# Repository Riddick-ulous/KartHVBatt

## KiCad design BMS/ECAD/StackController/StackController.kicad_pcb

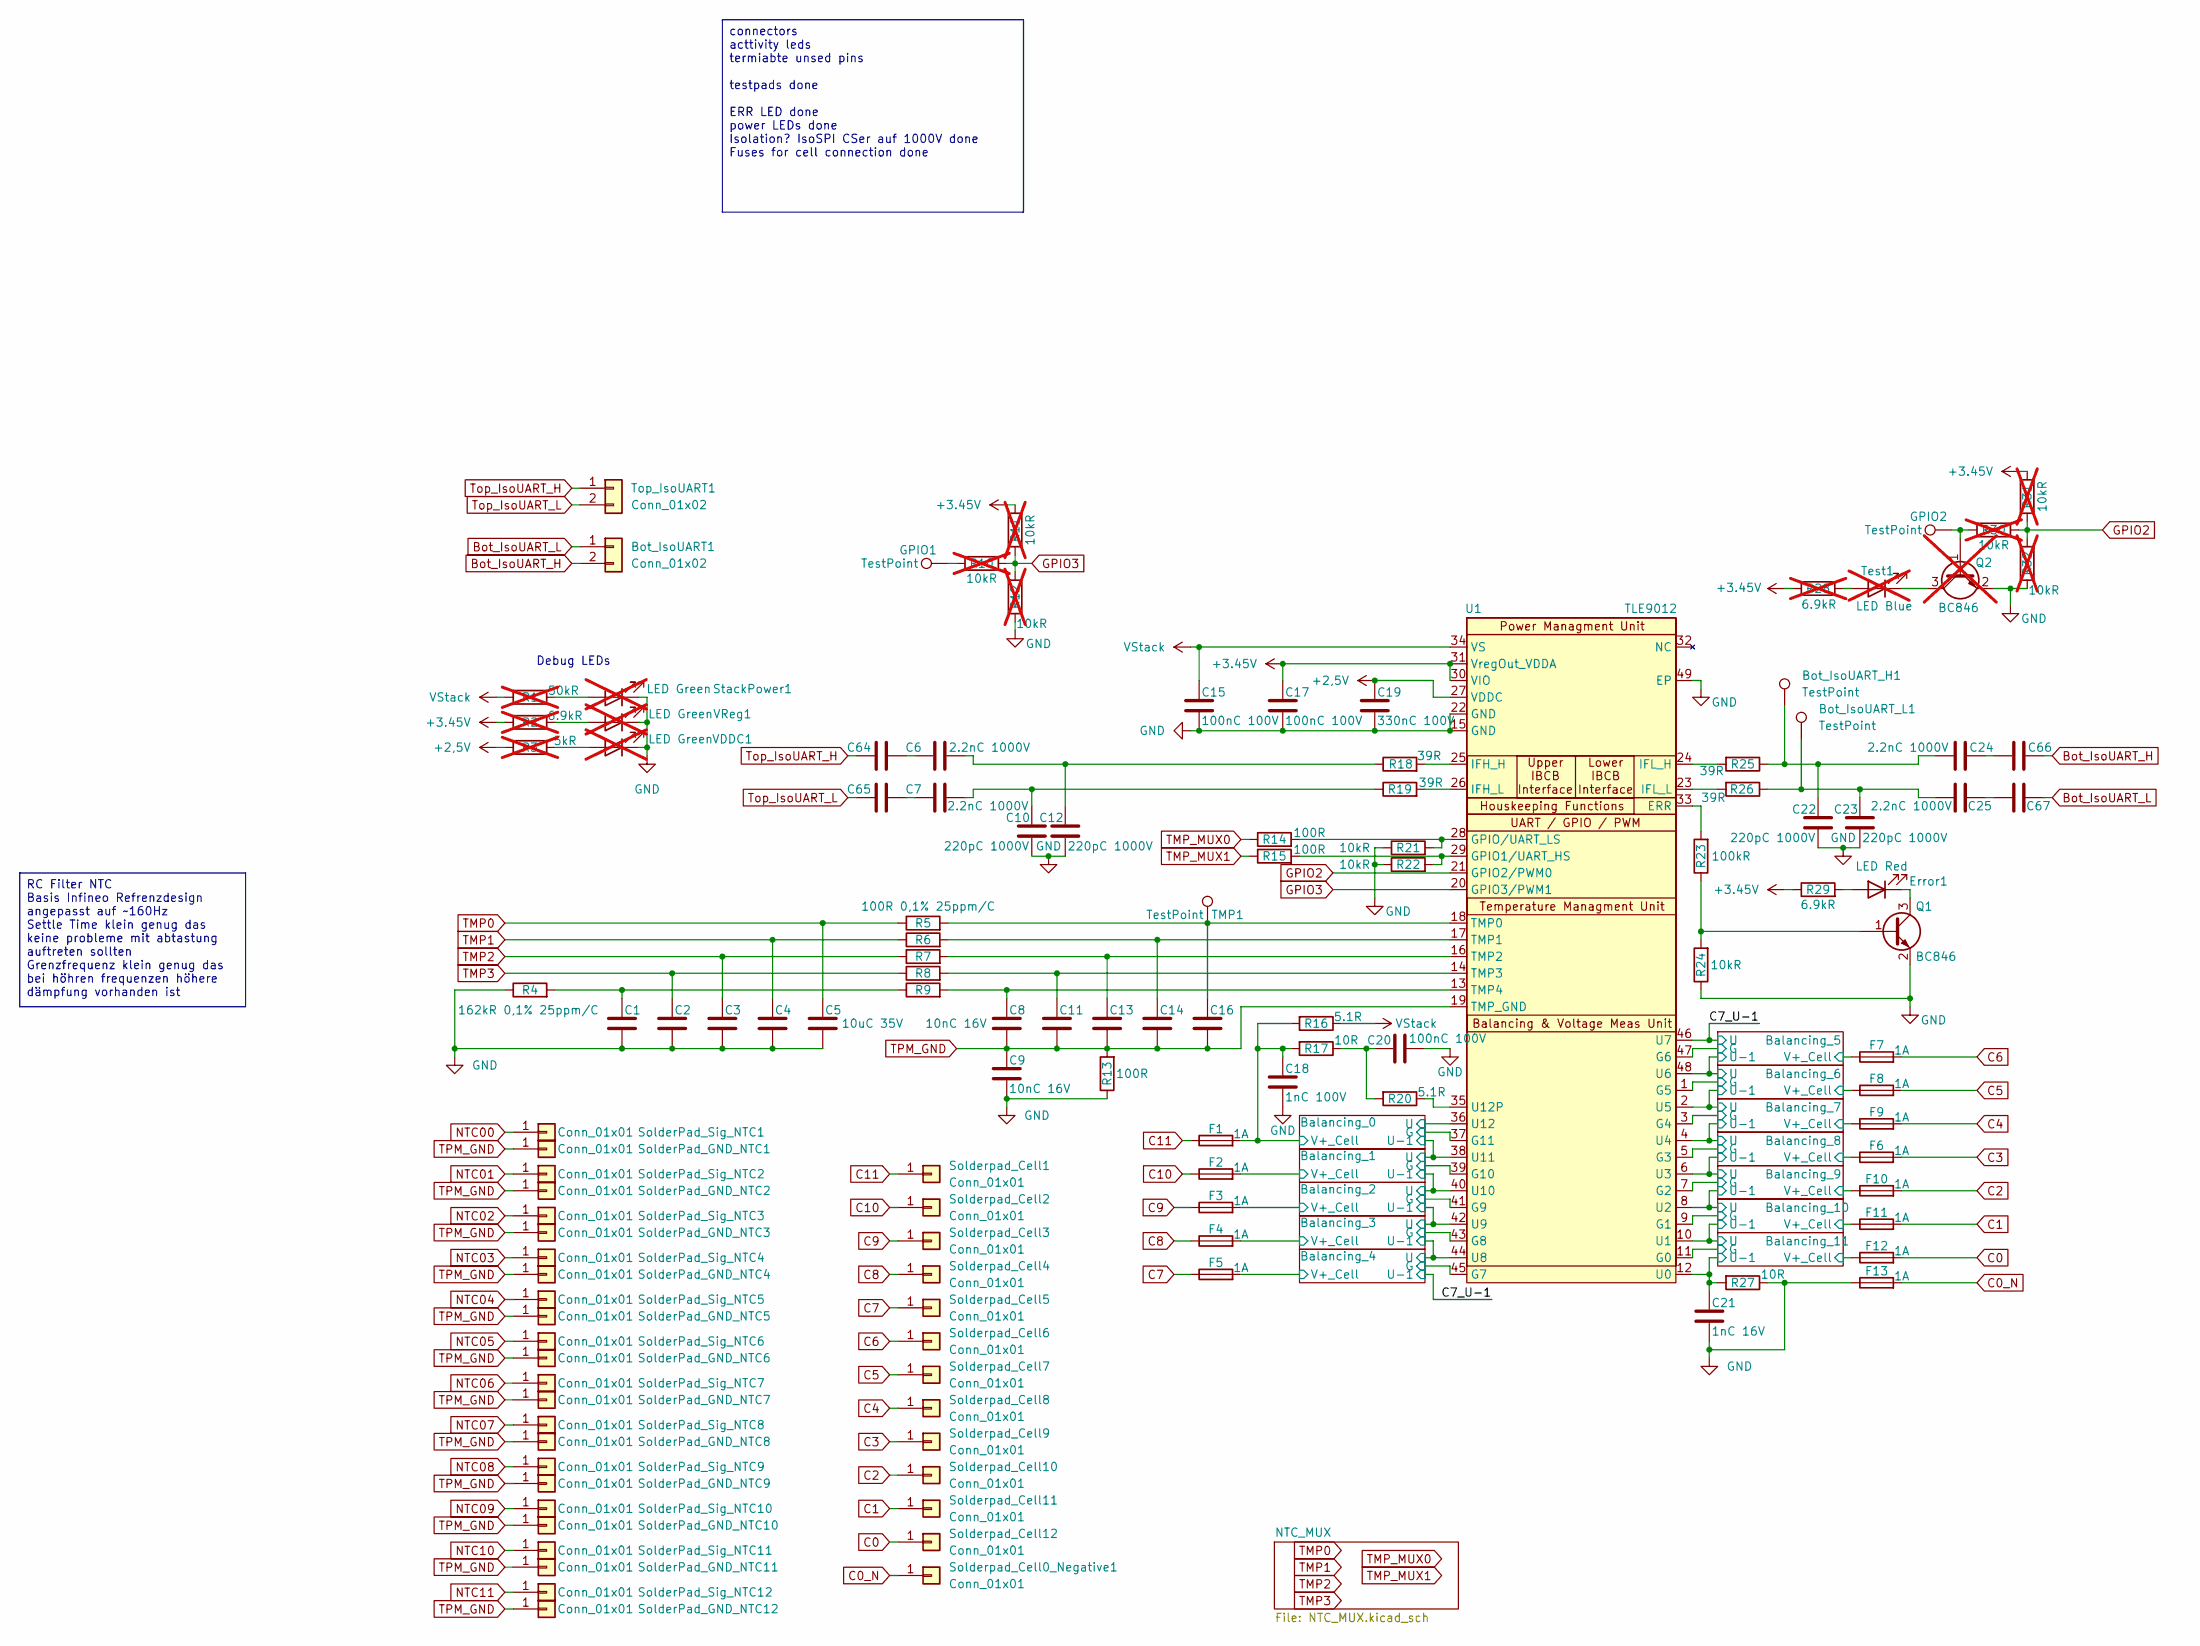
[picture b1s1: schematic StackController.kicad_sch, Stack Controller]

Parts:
Bot_IsoUART1: Conn_01x02; Molex_Micro-Fit_3.0_43045-0200_2x01_P3.00mm_Horizontal
Bot_IsoUART_H1: TestPoint; TestPoint_Loop_D1.80mm_Drill1.0mm_Beaded
Bot_IsoUART_L1: TestPoint; TestPoint_Loop_D1.80mm_Drill1.0mm_Beaded
C1, C2, C3, C4, C5: 10uC 35V; C_0805_2012Metric
C6, C7, C24, C25, C64, C65, C66, C67: 2.2nC 1000V; C_1206_3216Metric
C8, C9, C11, C13, C14, C16: 10nC 16V; C_0603_1608Metric
C10, C12, C22, C23: 220pC 1000V; C_1206_3216Metric
C15, C17, C20: 100nC 100V; C_0603_1608Metric
C18: 1nC 100V; C_0603_1608Metric
C19: 330nC 100V; C_0603_1608Metric
C21: 1nC 16V; C_0603_1608Metric
Error1: LED Red; LED_0805_2012Metric_Pad1.15x1.40mm_HandSolder
F1, F2, F3, F4, F5, F6, F7, F8, F9, F10, F11, F12, F13: 1A; Fuse_0603_1608Metric
GPIO1, GPIO2: TestPoint; TestPoint_Loop_D1.80mm_Drill1.0mm_Beaded
Q1: BC846; SOT-23
Q2: BC846; SOT-23; not fitted
R1: 50kR; R_0603_1608Metric; not fitted
R2, R28: 6.9kR; R_0603_1608Metric; not fitted
R3: 5kR; R_0603_1608Metric; not fitted
R4: 162kR 0,1% 25ppm/C; R_0603_1608Metric
R5, R6, R7, R8, R9: 100R 0,1% 25ppm/C; R_0603_1608Metric
R10, R11, R12, R30, R31, R32: 10kR; R_0603_1608Metric; not fitted
R13, R14, R15: 100R; R_0603_1608Metric
R16, R20: 5.1R; R_2512_6332Metric
R17, R27: 10R; R_2512_6332Metric
R18, R19, R25, R26: 39R; R_0603_1608Metric
R21, R22, R24: 10kR; R_0603_1608Metric
R23: 100kR; R_0603_1608Metric
R29: 6.9kR; R_0603_1608Metric
SolderPad_GND_NTC1, SolderPad_GND_NTC2, SolderPad_GND_NTC3, SolderPad_GND_NTC4, SolderPad_GND_NTC5, SolderPad_GND_NTC6, SolderPad_GND_NTC7, SolderPad_GND_NTC8, SolderPad_GND_NTC9, SolderPad_GND_NTC10, SolderPad_GND_NTC11, SolderPad_GND_NTC12: Conn_01x01; TestPoint_Pad_D1.5mm
SolderPad_Sig_NTC1, SolderPad_Sig_NTC2, SolderPad_Sig_NTC3, SolderPad_Sig_NTC4, SolderPad_Sig_NTC5, SolderPad_Sig_NTC6, SolderPad_Sig_NTC7, SolderPad_Sig_NTC8, SolderPad_Sig_NTC9, SolderPad_Sig_NTC10, SolderPad_Sig_NTC11, SolderPad_Sig_NTC12: Conn_01x01; TestPoint_Pad_D1.5mm
Solderpad_Cell0_Negative1, Solderpad_Cell1, Solderpad_Cell2, Solderpad_Cell3, Solderpad_Cell4, Solderpad_Cell5, Solderpad_Cell6, Solderpad_Cell7, Solderpad_Cell8, Solderpad_Cell9, Solderpad_Cell10, Solderpad_Cell11, Solderpad_Cell12: Conn_01x01; TestPoint_Pad_D3.0mm
StackPower1: LED Green; LED_0805_2012Metric_Pad1.15x1.40mm_HandSolder; not fitted
TMP1: TestPoint; TestPoint_Loop_D1.80mm_Drill1.0mm_Beaded
Test1: LED Blue; LED_0805_2012Metric_Pad1.15x1.40mm_HandSolder; not fitted
Top_IsoUART1: Conn_01x02; Molex_Micro-Fit_3.0_43045-0200_2x01_P3.00mm_Horizontal
U1: TLE9012; TQFP-48-1EP_7x7mm_P0.5mm_EP5x5mm
VDDC1: LED Green; LED_0805_2012Metric_Pad1.15x1.40mm_HandSolder; not fitted
VReg1: LED Green; LED_0805_2012Metric_Pad1.15x1.40mm_HandSolder; not fitted

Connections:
+2,5V: C19.1, R3.1, U1.27 (VDDC)
+3.45V: C17.1, R2.1, R11.2, R28.2, R29.1, R31.2, U1.30 (VIO), U1.31 (VregOut_VDDA)
/Balancing_0/G: U1.37 (G11); also elsewhere on the board
/Balancing_0/U: U1.36 (U12); also elsewhere on the board
/Balancing_0/U-1: U1.38 (U11); also elsewhere on the board
/Balancing_0/V+_Cell: C18.1, F1.2, R16.2, R17.2; also elsewhere on the board
/Balancing_1/G: U1.39 (G10); also elsewhere on the board
/Balancing_1/U-1: U1.40 (U10); also elsewhere on the board
/Balancing_1/V+_Cell: F2.2; also elsewhere on the board
/Balancing_2/G: U1.41 (G9); also elsewhere on the board
/Balancing_2/U-1: U1.42 (U9); also elsewhere on the board
/Balancing_2/V+_Cell: F3.2; also elsewhere on the board
/Balancing_3/G: U1.43 (G8); also elsewhere on the board
/Balancing_3/U-1: U1.44 (U8); also elsewhere on the board
/Balancing_3/V+_Cell: F4.2; also elsewhere on the board
/Balancing_4/G: U1.45 (G7); also elsewhere on the board
/Balancing_4/V+_Cell: F5.2; also elsewhere on the board
/Balancing_5/G: U1.47 (G6); also elsewhere on the board
/Balancing_5/U-1: U1.48 (U6); also elsewhere on the board
/Balancing_5/V+_Cell: F7.1; also elsewhere on the board
/Balancing_6/G: U1.1 (G5); also elsewhere on the board
/Balancing_6/U-1: U1.2 (U5); also elsewhere on the board
/Balancing_6/V+_Cell: F8.1; also elsewhere on the board
/Balancing_7/G: U1.3 (G4); also elsewhere on the board
/Balancing_7/U-1: U1.4 (U4); also elsewhere on the board
/Balancing_7/V+_Cell: F9.1; also elsewhere on the board
/Balancing_8/G: U1.5 (G3); also elsewhere on the board
/Balancing_8/U-1: U1.6 (U3); also elsewhere on the board
/Balancing_8/V+_Cell: F6.1; also elsewhere on the board
/Balancing_9/G: U1.7 (G2); also elsewhere on the board
/Balancing_9/V+_Cell: F10.1; also elsewhere on the board
/Balancing_10/G: U1.9 (G1); also elsewhere on the board
/Balancing_10/U: U1.8 (U2); also elsewhere on the board
/Balancing_10/U-1: U1.10 (U1); also elsewhere on the board
/Balancing_10/V+_Cell: F11.1; also elsewhere on the board
/Balancing_11/G: U1.11 (G0); also elsewhere on the board
/Balancing_11/U-1: C21.1, R27.2, U1.12 (U0); also elsewhere on the board
/Balancing_11/V+_Cell: F12.1; also elsewhere on the board
/C7_U-1: U1.46 (U7); also elsewhere on the board
Bot_IsoUART_H: Bot_IsoUART1.2, C66.1; also elsewhere on the board
Bot_IsoUART_L: Bot_IsoUART1.1, C67.1; also elsewhere on the board
C0: F12.2, Solderpad_Cell12.1 (Pin_1_1)
C0_N: F13.2, Solderpad_Cell0_Negative1.1 (Pin_1_1)
C1: F11.2, Solderpad_Cell11.1 (Pin_1_1)
C2: F10.2, Solderpad_Cell10.1 (Pin_1_1)
C3: F6.2, Solderpad_Cell9.1 (Pin_1_1)
C4: F9.2, Solderpad_Cell8.1 (Pin_1_1)
C5: F8.2, Solderpad_Cell7.1 (Pin_1_1)
C6: F7.2, Solderpad_Cell6.1 (Pin_1_1)
C7: F5.1, Solderpad_Cell5.1 (Pin_1_1)
C8: F4.1, Solderpad_Cell4.1 (Pin_1_1)
C9: F3.1, Solderpad_Cell3.1 (Pin_1_1)
C10: F2.1, Solderpad_Cell2.1 (Pin_1_1)
C11: F1.1, Solderpad_Cell1.1 (Pin_1_1)
GND: C1.2, C2.2, C3.2, C4.2, C5.2, C9.2, C10.2, C12.2, C15.2, C17.2, C18.2, C19.2, C20.1, C21.2, C22.2, C23.2, F13.1, Q1.2 (E), Q2.2 (E), R4.1, R12.1, R13.1, R21.1, R22.1, R24.1, R27.1, R32.1, StackPower1.1 (K), U1.15 (GND), U1.22 (GND), U1.49 (EP), VDDC1.1 (K), VReg1.1 (K); also elsewhere on the board
GPIO2: R30.2, R31.1, R32.2, U1.21 (GPIO2/PWM0)
GPIO3: R10.2, R11.1, R12.2, U1.20 (GPIO3/PWM1)
NTC00: SolderPad_Sig_NTC1.1 (Pin_1_1); also elsewhere on the board
NTC01: SolderPad_Sig_NTC2.1 (Pin_1_1); also elsewhere on the board
NTC02: SolderPad_Sig_NTC3.1 (Pin_1_1); also elsewhere on the board
NTC03: SolderPad_Sig_NTC4.1 (Pin_1_1); also elsewhere on the board
NTC04: SolderPad_Sig_NTC5.1 (Pin_1_1); also elsewhere on the board
NTC05: SolderPad_Sig_NTC6.1 (Pin_1_1); also elsewhere on the board
NTC06: SolderPad_Sig_NTC7.1 (Pin_1_1); also elsewhere on the board
NTC07: SolderPad_Sig_NTC8.1 (Pin_1_1); also elsewhere on the board
NTC08: SolderPad_Sig_NTC9.1 (Pin_1_1); also elsewhere on the board
NTC09: SolderPad_Sig_NTC10.1 (Pin_1_1); also elsewhere on the board
NTC10: SolderPad_Sig_NTC11.1 (Pin_1_1); also elsewhere on the board
NTC11: SolderPad_Sig_NTC12.1 (Pin_1_1); also elsewhere on the board
unnamed: Bot_IsoUART_H1.1 (1_1), C22.1, C24.2, R25.1
unnamed: Bot_IsoUART_L1.1 (1_1), C23.1, C25.2, R26.1
unnamed: C1.1, R4.2, R9.1
unnamed: C6.2, C64.1
unnamed: C7.1, C10.1, R19.1
unnamed: C6.1, C12.1, R18.1
unnamed: C20.2, R17.1, R20.2
unnamed: C24.1, C66.2
unnamed: C25.1, C67.2
unnamed: C7.2, C65.1
unnamed: Error1.2 (A), R29.2
unnamed: Error1.1 (K), Q1.3 (C)
unnamed: GPIO1.1 (1_1), R10.1
unnamed: Q1.1 (B), R23.1, R24.2
unnamed: GPIO2.1 (1_1), Q2.1 (B), R30.1
unnamed: Q2.3 (C), Test1.1 (K)
unnamed: R1.2, StackPower1.2 (A)
unnamed: R28.1, Test1.2 (A)
unnamed: R23.2, U1.33 (ERR)
unnamed: R15.2, R22.2, U1.29 (GPIO1/UART_HS)
unnamed: R14.2, R21.2, U1.28 (GPIO/UART_LS)
unnamed: R18.2, U1.25 (IFH_H)
unnamed: R19.2, U1.26 (IFH_L)
unnamed: R25.2, U1.24 (IFL_H)
unnamed: R26.2, U1.23 (IFL_L)
unnamed: C16.1, R5.2, TMP1.1 (1_1), U1.18 (TMP0)
unnamed: C14.1, R6.2, U1.17 (TMP1)
unnamed: C13.1, R7.2, U1.16 (TMP2)
unnamed: C11.1, R8.2, U1.14 (TMP3)
unnamed: C8.1, R9.2, U1.13 (TMP4)
unnamed: R20.1, U1.35 (U12P)
unnamed: R3.2, VDDC1.2 (A)
unnamed: R2.2, VReg1.2 (A)
TMP0: C5.1, R5.1; also elsewhere on the board
TMP1: C4.1, R6.1; also elsewhere on the board
TMP2: C3.1, R7.1; also elsewhere on the board
TMP3: C2.1, R8.1; also elsewhere on the board
TMP_MUX0: R14.1; also elsewhere on the board
TMP_MUX1: R15.1; also elsewhere on the board
TPM_GND: C8.2, C9.1, C11.2, C13.2, C14.2, C16.2, R13.2, SolderPad_GND_NTC1.1 (Pin_1_1), SolderPad_GND_NTC2.1 (Pin_1_1), SolderPad_GND_NTC3.1 (Pin_1_1), SolderPad_GND_NTC4.1 (Pin_1_1), SolderPad_GND_NTC5.1 (Pin_1_1), SolderPad_GND_NTC6.1 (Pin_1_1), SolderPad_GND_NTC7.1 (Pin_1_1), SolderPad_GND_NTC8.1 (Pin_1_1), SolderPad_GND_NTC9.1 (Pin_1_1), SolderPad_GND_NTC10.1 (Pin_1_1), SolderPad_GND_NTC11.1 (Pin_1_1), SolderPad_GND_NTC12.1 (Pin_1_1), U1.19 (TMP_GND); also elsewhere on the board
Top_IsoUART_H: C64.2, Top_IsoUART1.1; also elsewhere on the board
Top_IsoUART_L: C65.2, Top_IsoUART1.2; also elsewhere on the board
VStack: C15.1, R1.1, R16.1, U1.34 (VS)

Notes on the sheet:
Debug LEDs
connectors acttivity leds termiabte unsed pins testpads done ERR LED done power LEDs done Isolation? IsoSPI CSer auf 1000V done Fuses for cell connection done
RC Filter NTC Basis Infineo Refrenzdesign angepasst auf ~160Hz Settle Time klein genug das keine probleme mit abtastung auftreten sollten Grenzfrequenz klein genug das bei höhren frequenzen höhere dämpfung vorhanden ist

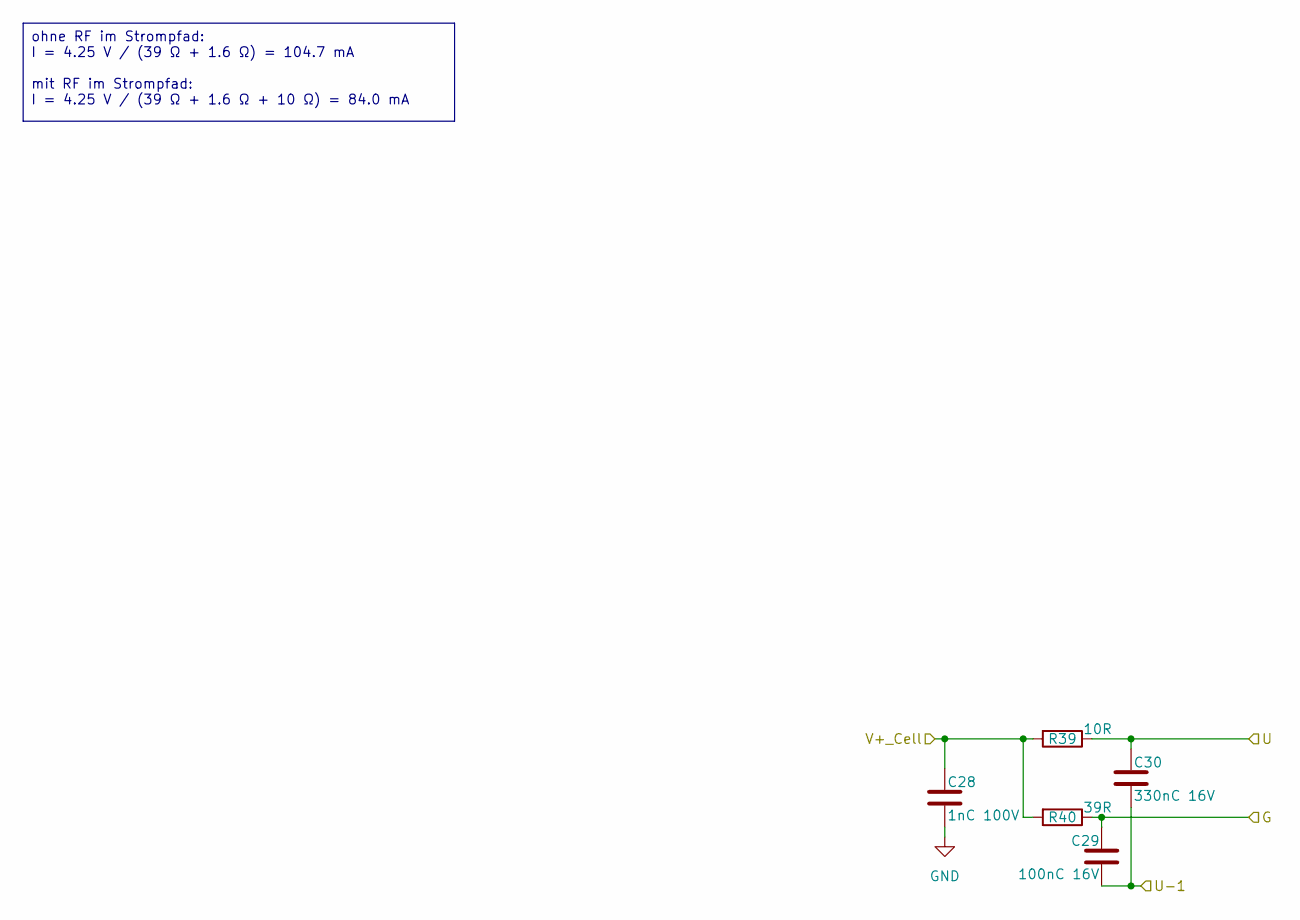
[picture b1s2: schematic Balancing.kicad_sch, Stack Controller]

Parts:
C28: 1nC 100V; C_0603_1608Metric
C29: 100nC 16V; C_0603_1608Metric
C30: 330nC 16V; C_0603_1608Metric
R39: 10R; R_2512_6332Metric
R40: 39R; R_2512_6332Metric

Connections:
/Balancing_0/G: C29.1, R40.1; also elsewhere on the board
/Balancing_0/U: C30.1, R39.1; also elsewhere on the board
/Balancing_0/U-1: C29.2, C30.2; also elsewhere on the board
/Balancing_0/V+_Cell: C28.1, R39.2, R40.2; also elsewhere on the board
GND: C28.2; also elsewhere on the board

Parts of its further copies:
C31, C34, C37, C40, C43, C46, C49, C52, C55, C58, C61: 1nC 100V; C_0603_1608Metric
C32, C35, C38, C41, C44, C47, C50, C53, C56, C59, C62: 100nC 16V; C_0603_1608Metric
C33, C36, C39, C42, C45, C48, C51, C54, C57, C60, C63: 330nC 16V; C_0603_1608Metric
R41, R43, R45, R47, R49, R51, R53, R55, R57, R59, R61: 10R; R_2512_6332Metric
R42, R44, R46, R48, R50, R52, R54, R56, R58, R60, R62: 39R; R_2512_6332Metric

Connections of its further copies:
/Balancing_0/U-1: C33.1, R41.1; also elsewhere on the board
/Balancing_1/G: C32.1, R42.1; also elsewhere on the board
/Balancing_1/U-1: C32.2, C33.2, C36.1, R43.1; also elsewhere on the board
/Balancing_1/V+_Cell: C31.1, R41.2, R42.2; also elsewhere on the board
/Balancing_2/G: C35.1, R44.1; also elsewhere on the board
/Balancing_2/U-1: C35.2, C36.2, C39.1, R45.1; also elsewhere on the board
/Balancing_2/V+_Cell: C34.1, R43.2, R44.2; also elsewhere on the board
/Balancing_3/G: C38.1, R46.1; also elsewhere on the board
/Balancing_3/U-1: C38.2, C39.2, C42.1, R47.1; also elsewhere on the board
/Balancing_3/V+_Cell: C37.1, R45.2, R46.2; also elsewhere on the board
/Balancing_4/G: C41.1, R48.1; also elsewhere on the board
/Balancing_4/V+_Cell: C40.1, R47.2, R48.2; also elsewhere on the board
/Balancing_5/G: C44.1, R50.1; also elsewhere on the board
/Balancing_5/U-1: C44.2, C45.2, C48.1, R51.1; also elsewhere on the board
/Balancing_5/V+_Cell: C43.1, R49.2, R50.2; also elsewhere on the board
/Balancing_6/G: C47.1, R52.1; also elsewhere on the board
/Balancing_6/U-1: C47.2, C48.2, C51.1, R53.1; also elsewhere on the board
/Balancing_6/V+_Cell: C46.1, R51.2, R52.2; also elsewhere on the board
/Balancing_7/G: C50.1, R54.1; also elsewhere on the board
/Balancing_7/U-1: C50.2, C51.2, C54.1, R55.1; also elsewhere on the board
/Balancing_7/V+_Cell: C49.1, R53.2, R54.2; also elsewhere on the board
/Balancing_8/G: C53.1, R56.1; also elsewhere on the board
/Balancing_8/U-1: C53.2, C54.2, C57.1, R57.1; also elsewhere on the board
/Balancing_8/V+_Cell: C52.1, R55.2, R56.2; also elsewhere on the board
/Balancing_9/G: C56.1, R58.1; also elsewhere on the board
/Balancing_9/V+_Cell: C55.1, R57.2, R58.2; also elsewhere on the board
/Balancing_10/G: C59.1, R60.1; also elsewhere on the board
/Balancing_10/U: C56.2, C57.2, C60.1, R59.1; also elsewhere on the board
/Balancing_10/U-1: C59.2, C60.2, C63.1, R61.1; also elsewhere on the board
/Balancing_10/V+_Cell: C58.1, R59.2, R60.2; also elsewhere on the board
/Balancing_11/G: C62.1, R62.1; also elsewhere on the board
/Balancing_11/U-1: C62.2, C63.2; also elsewhere on the board
/Balancing_11/V+_Cell: C61.1, R61.2, R62.2; also elsewhere on the board
/C7_U-1: C41.2, C42.2, C45.1, R49.1; also elsewhere on the board
GND: C31.2, C34.2, C37.2, C40.2, C43.2, C46.2, C49.2, C52.2, C55.2, C58.2, C61.2; also elsewhere on the board

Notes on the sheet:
ohne RF im Strompfad: I = 4.25 V / (39 Ω + 1.6 Ω) = 104.7 mA mit RF im Strompfad: I = 4.25 V / (39 Ω + 1.6 Ω + 10 Ω) = 84.0 mA

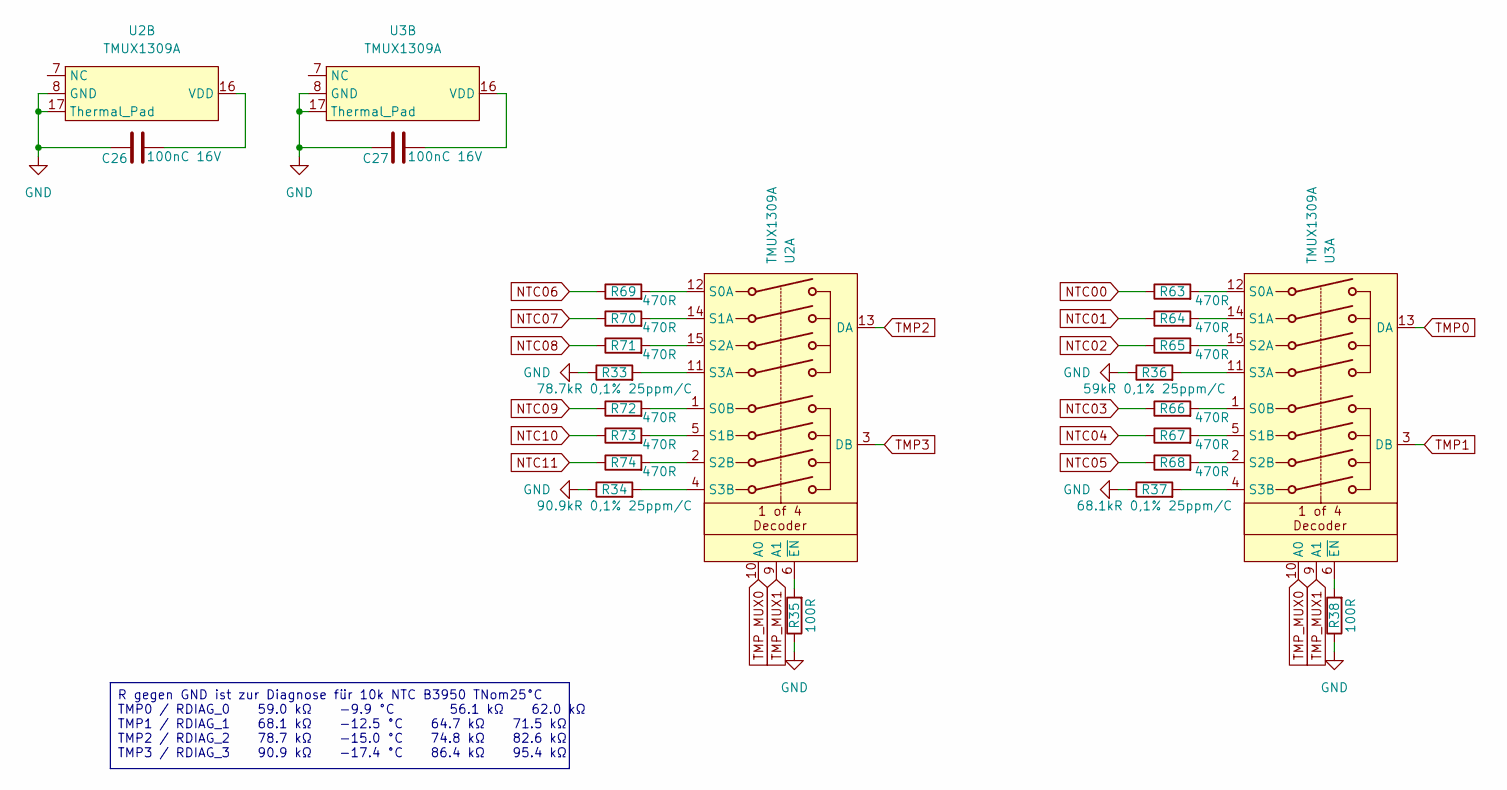
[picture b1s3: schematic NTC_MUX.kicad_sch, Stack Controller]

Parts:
C26, C27: 100nC 16V; C_0603_1608Metric
R33: 78.7kR 0,1% 25ppm/C; R_0603_1608Metric
R34: 90.9kR 0,1% 25ppm/C; R_0603_1608Metric
R35, R38: 100R; R_0603_1608Metric
R36: 59kR 0,1% 25ppm/C; R_0603_1608Metric
R37: 68.1kR 0,1% 25ppm/C; R_0603_1608Metric
R63, R64, R65, R66, R67, R68, R69, R70, R71, R72, R73, R74: 470R; R_0603_1608Metric
U2, U3: TMUX1309A; TSSOP-16_4.4x5mm_P0.65mm

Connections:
GND: C26.1, C27.1, R33.1, R34.1, R35.1, R36.1, R37.1, R38.1, U2.8 (GND), U2.17 (Thermal_Pad), U3.8 (GND), U3.17 (Thermal_Pad); also elsewhere on the board
NTC00: R63.1; also elsewhere on the board
NTC01: R64.1; also elsewhere on the board
NTC02: R65.1; also elsewhere on the board
NTC03: R66.1; also elsewhere on the board
NTC04: R67.1; also elsewhere on the board
NTC05: R68.1; also elsewhere on the board
NTC06: R69.1; also elsewhere on the board
NTC07: R70.1; also elsewhere on the board
NTC08: R71.1; also elsewhere on the board
NTC09: R72.1; also elsewhere on the board
NTC10: R73.1; also elsewhere on the board
NTC11: R74.1; also elsewhere on the board
unnamed: R69.2, U2.12 (S0A)
unnamed: R72.2, U2.1 (S0B)
unnamed: R70.2, U2.14 (S1A)
unnamed: R73.2, U2.5 (S1B)
unnamed: R71.2, U2.15 (S2A)
unnamed: R74.2, U2.2 (S2B)
unnamed: R33.2, U2.11 (S3A)
unnamed: R34.2, U2.4 (S3B)
unnamed: R35.2, U2.6 (~EN)
unnamed: C26.2, U2.16 (VDD)
unnamed: R63.2, U3.12 (S0A)
unnamed: R66.2, U3.1 (S0B)
unnamed: R64.2, U3.14 (S1A)
unnamed: R67.2, U3.5 (S1B)
unnamed: R65.2, U3.15 (S2A)
unnamed: R68.2, U3.2 (S2B)
unnamed: R36.2, U3.11 (S3A)
unnamed: R37.2, U3.4 (S3B)
unnamed: R38.2, U3.6 (~EN)
unnamed: C27.2, U3.16 (VDD)
TMP0: U3.13 (DA); also elsewhere on the board
TMP1: U3.3 (DB); also elsewhere on the board
TMP2: U2.13 (DA); also elsewhere on the board
TMP3: U2.3 (DB); also elsewhere on the board
TMP_MUX0: U2.10 (A0), U3.10 (A0); also elsewhere on the board
TMP_MUX1: U2.9 (A1), U3.9 (A1); also elsewhere on the board

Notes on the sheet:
R gegen GND ist zur Diagnose für 10k NTC B3950 TNom25°C TMP0 / RDIAG_0 59.0 kΩ −9.9 °C 56.1 kΩ 62.0 kΩ TMP1 / RDIAG_1 68.1 kΩ −12.5 °C 64.7 kΩ 71.5 kΩ TMP2 / RDIAG_2 78.7 kΩ −15.0 °C 74.8 kΩ 82.6 kΩ TMP3 / RDIAG_3 90.9 kΩ −17.4 °C 86.4 kΩ 95.4 kΩ

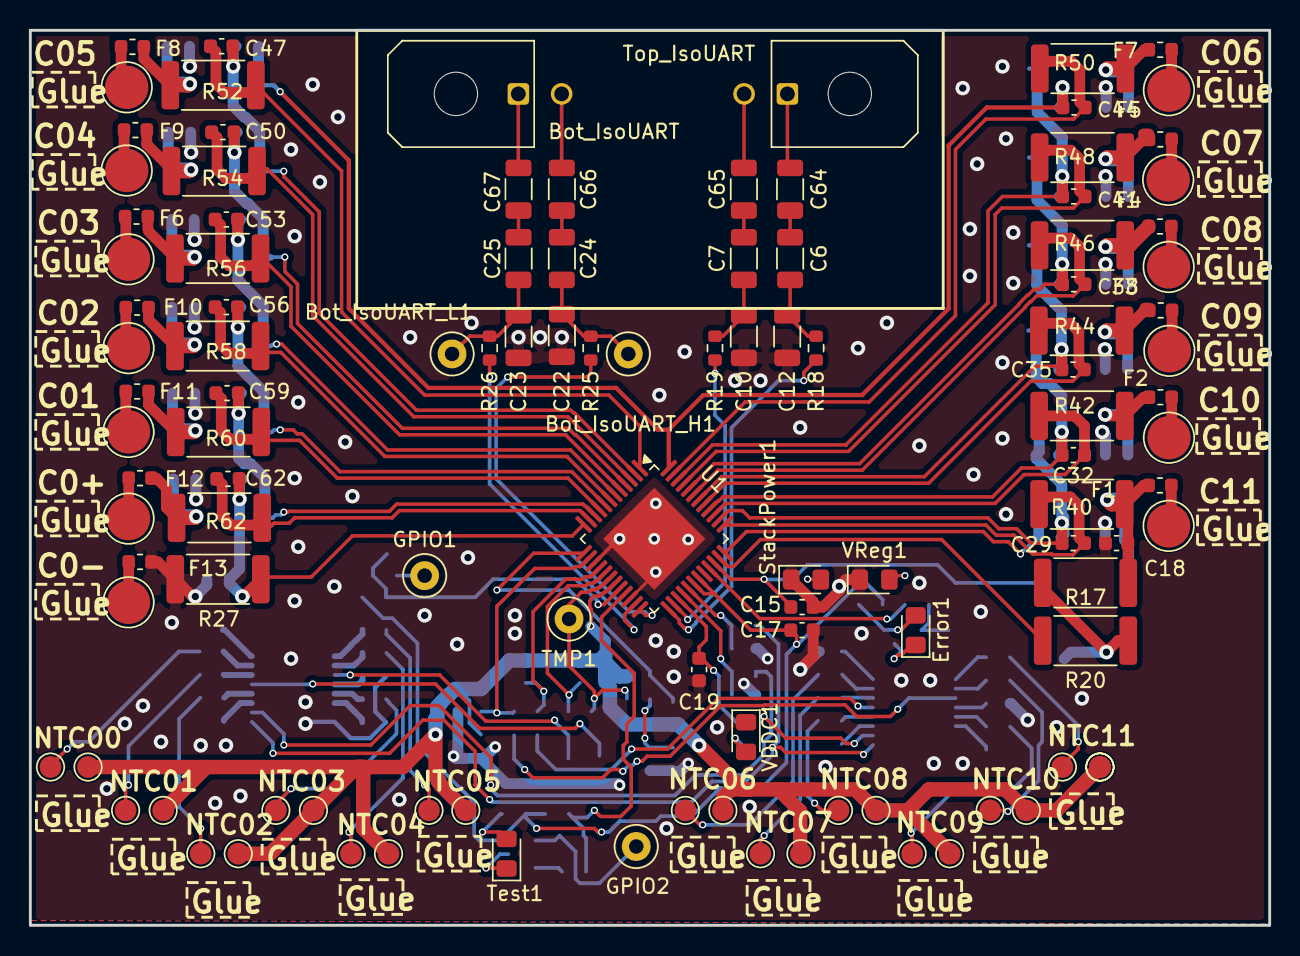
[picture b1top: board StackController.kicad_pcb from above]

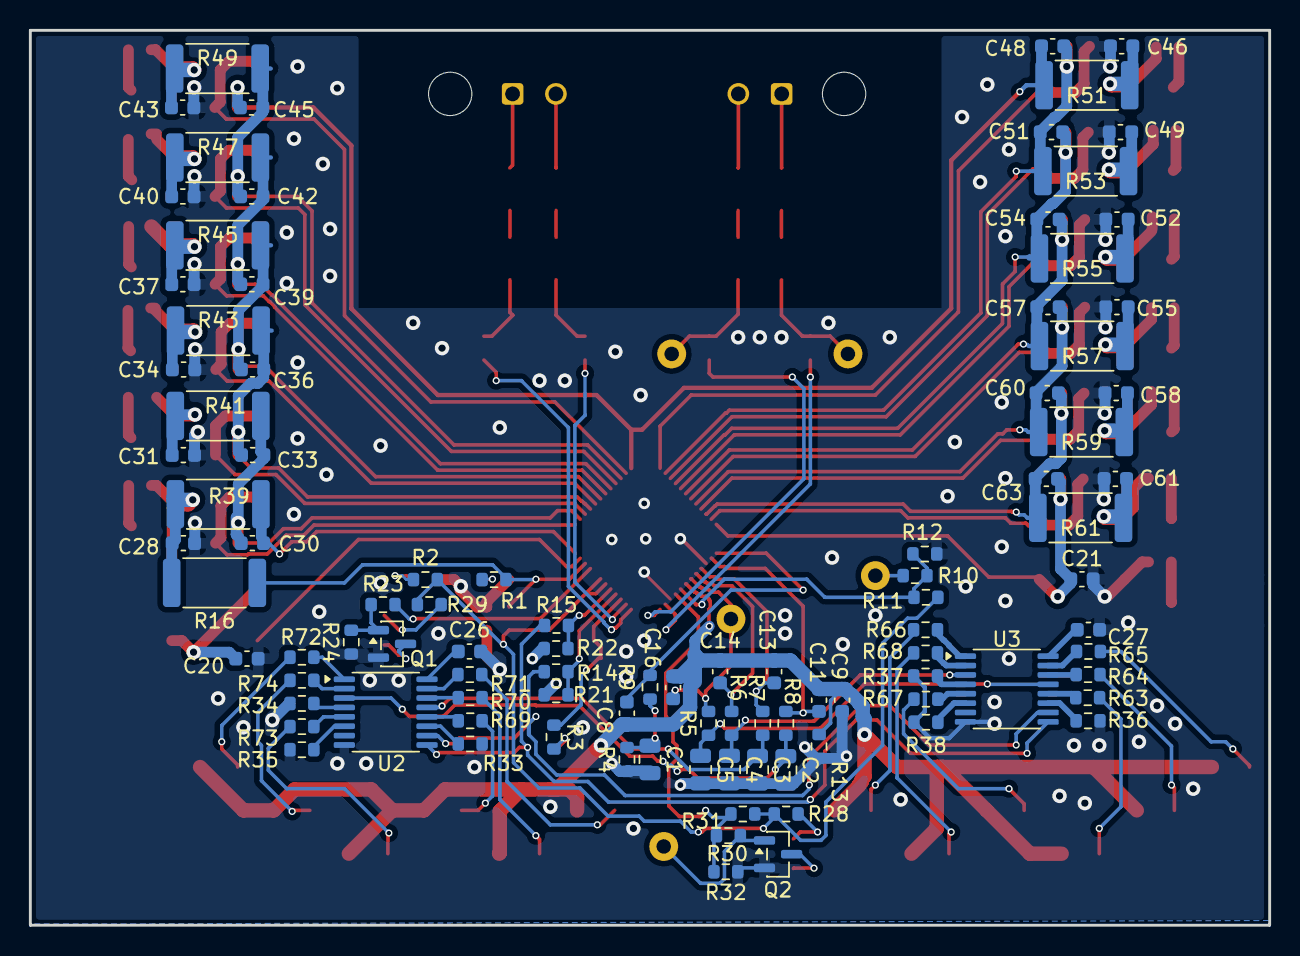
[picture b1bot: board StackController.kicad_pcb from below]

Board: 2 copper layers, 85.8 x 62.0 mm, 209 parts (98 on the bottom side), 132 nets.

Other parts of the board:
Bot_IsoUART: Conn_01x02; Molex_Micro-Fit_3.0_43045-0200_2x01_P3.00mm_Horizontal
SolderPad_GND_NTC12#2: Conn_01x01; TestPoint_Pad_D1.5mm
Top_IsoUART: Conn_01x02; Molex_Micro-Fit_3.0_43045-0200_2x01_P3.00mm_Horizontal

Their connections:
Bot_IsoUART_H: Bot_IsoUART.2; also elsewhere on the board
Bot_IsoUART_L: Bot_IsoUART.1; also elsewhere on the board
TPM_GND: SolderPad_GND_NTC12#2.1 (Pin_1_1); also elsewhere on the board
Top_IsoUART_H: Top_IsoUART.1; also elsewhere on the board
Top_IsoUART_L: Top_IsoUART.2; also elsewhere on the board

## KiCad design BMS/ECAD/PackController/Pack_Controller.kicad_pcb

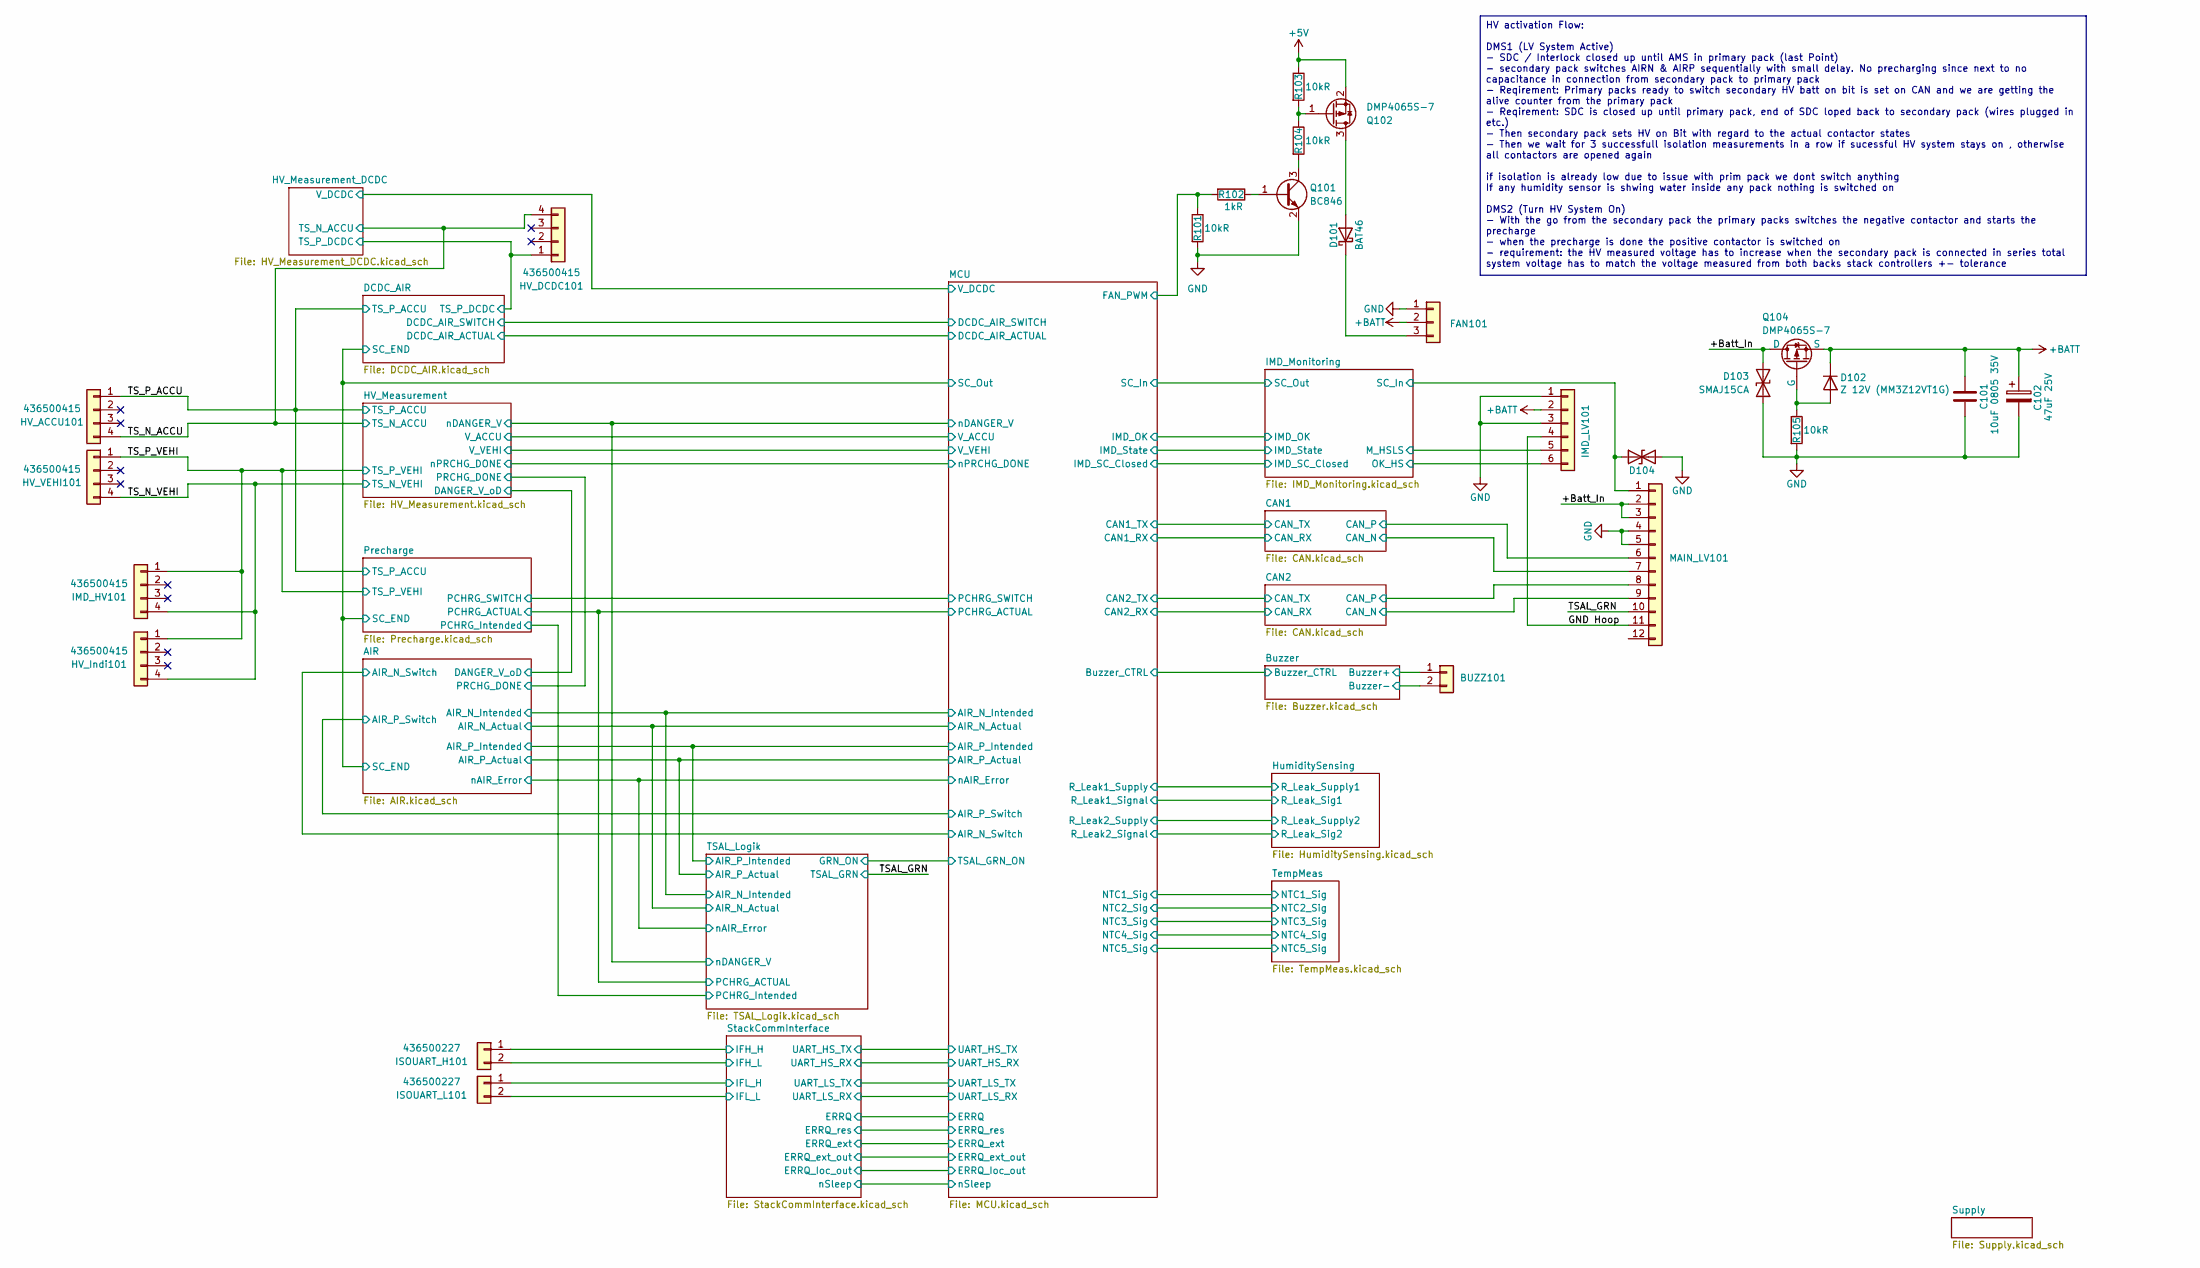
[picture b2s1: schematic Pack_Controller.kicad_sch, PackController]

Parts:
BUZZ101: Molex_Micro-Fit_3.0_43650-0215_1x02_P3.00mm_Vertical
C101: 10uF 0805 35V; C_0805_2012Metric
C102: 47uF 25V; CP_Radial_D6.3mm_P2.50mm
D101: BAT46; D_SOD-123
D102: Z 12V (MM3Z12VT1G); D_SOD-323_HandSoldering; PartNr. MM3Z3V3T1G
D103: SMAJ15CA; D_SMA
D104: DESD5V0S1BA-7; D_SOD-323
FAN101: Molex_Micro-Fit_3.0_43650-0315_1x03_P3.00mm_Vertical
HV_ACCU101: 436500415; Molex_Micro-Fit_3.0_43650-0415_1x04_P3.00mm_Vertical
HV_DCDC101: 436500415; Molex_Micro-Fit_3.0_43650-0415_1x04_P3.00mm_Vertical
HV_Indi101: 436500415; Molex_Micro-Fit_3.0_43650-0415_1x04_P3.00mm_Vertical
HV_VEHI101: 436500415; Molex_Micro-Fit_3.0_43650-0415_1x04_P3.00mm_Vertical
IMD_HV101: 436500415; Molex_Micro-Fit_3.0_43650-0415_1x04_P3.00mm_Vertical
IMD_LV101: Molex_Micro-Fit_3.0_43045-0612_2x03_P3.00mm_Vertical
ISOUART_H101: 436500227; Molex_Micro-Fit_3.0_43650-0215_1x02_P3.00mm_Vertical
ISOUART_L101: 436500227; Molex_Micro-Fit_3.0_43650-0215_1x02_P3.00mm_Vertical
MAIN_LV101: Molex_Micro-Fit_3.0_43045-1212_2x06_P3.00mm_Vertical
Q101: BC846; SOT-23
Q102, Q104: DMP4065S-7; SOT-23-3
R101, R103, R104, R105: 10kR; R_0603_1608Metric
R102: 1kR; R_0603_1608Metric

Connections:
+5V: Q102.2 (S), R103.1; also elsewhere on the board
+BATT: C101.2, C102.1, D102.1 (K), FAN101.2, IMD_LV101.2, Q104.3 (S); also elsewhere on the board
/+Batt_In: D103.2 (A2), MAIN_LV101.2, MAIN_LV101.3, Q104.1 (D)
/Buzzer/Buzzer+: BUZZ101.1; also elsewhere on the board
/Buzzer/Buzzer-: BUZZ101.2; also elsewhere on the board
/CAN1/CAN_N: MAIN_LV101.7; also elsewhere on the board
/CAN1/CAN_P: MAIN_LV101.6; also elsewhere on the board
/CAN2/CAN_N: MAIN_LV101.9; also elsewhere on the board
/CAN2/CAN_P: MAIN_LV101.8; also elsewhere on the board
/DCDC_AIR/TS_P_DCDC: HV_DCDC101.1; also elsewhere on the board
/GND Hoop: IMD_LV101.4, MAIN_LV101.11
/IMD_Monitoring/M_HSLS: IMD_LV101.5; also elsewhere on the board
/IMD_Monitoring/OK_HS: IMD_LV101.6; also elsewhere on the board
/IMD_Monitoring/SC_In: D104.1 (A1), MAIN_LV101.1; also elsewhere on the board
/MCU/FAN_PWM: R101.1, R102.2; also elsewhere on the board
/StackCommInterface/IFH_H: ISOUART_H101.1; also elsewhere on the board
/StackCommInterface/IFH_L: ISOUART_H101.2; also elsewhere on the board
/StackCommInterface/IFL_H: ISOUART_L101.1; also elsewhere on the board
/StackCommInterface/IFL_L: ISOUART_L101.2; also elsewhere on the board
/TSAL_GRN: MAIN_LV101.10; also elsewhere on the board
/TS_N_ACCU: HV_ACCU101.4, HV_DCDC101.4; also elsewhere on the board
/TS_N_VEHI: HV_Indi101.4, HV_VEHI101.4, IMD_HV101.4; also elsewhere on the board
/TS_P_ACCU: HV_ACCU101.1; also elsewhere on the board
/TS_P_VEHI: HV_Indi101.1, HV_VEHI101.1, IMD_HV101.1; also elsewhere on the board
GND: C101.1, C102.2, D103.1 (A1), D104.2 (A2), FAN101.1, IMD_LV101.1, IMD_LV101.3, MAIN_LV101.4, MAIN_LV101.5, Q101.2 (E), R101.2, R105.2; also elsewhere on the board
unnamed: D101.2 (A), Q102.3 (D)
unnamed: D101.1 (K), FAN101.3
unnamed: D102.2 (A), Q104.2 (G), R105.1
unnamed: Q101.1 (B), R102.1
unnamed: Q101.3 (C), R104.2
unnamed: Q102.1 (G), R103.2, R104.1

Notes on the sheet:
HV activation Flow: DMS1 (LV System Active) - SDC / Interlock closed up until AMS in primary pack (last Point) - secondary pack switches AIRN & AIRP sequentially with small delay. No precharging since next to no capacitance in connection from secondary pack to primary pack - Reqirement: Primary pac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
